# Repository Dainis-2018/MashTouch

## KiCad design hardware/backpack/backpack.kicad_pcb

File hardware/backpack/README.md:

# I/O backpack (KiCad 10)

The MCU-less board that plugs into J8 of the Waveshare ESP32‑S3‑Touch‑LCD‑3.5. What it does and why: `docs/design.md` (*I/O backpack PCB*). Mechanics, zones and connector order: `docs/backpack-layout.md`.

| File | Contents |
|---|---|
| `backpack.kicad_pro` | the project: open this in KiCad |
| `backpack.kicad_sch` | the whole schematic on one A3 sheet, **wired**: J8 in the middle, outputs (OUT1–4, PWR1–2, JP1) on the left, the 12 V input and buck on top, PT100 (2× MAX31865, JP2/JP3, J4), 1‑Wire, level and the front panel (TCA9535, J7) on the right, decoupling, power flags and holes at the bottom. Power nets are symbols; every other net has one label with its name |
| `backpack.kicad_sym`, `sym-lib-table` | project symbols: MOSFETs, the ICs, J8 and the terminals, with the pins where the sheet needs them |
| `backpack.kicad_pcb` | outline with the antenna notch, holes, J8 and terminals at their measured positions; all parts placed (zones and reasons in `docs/backpack-layout.md`), silkscreen labels done, **routed** (two layers, GND pour on both) |
| `backpack.pretty/`, `fp-lib-table` | project footprints: the J8 header for the back side |
| `netlist-reference.txt` | the reviewed netlist, pin by pin, for `tools/kicad/netcheck.js` |
| `parts.csv` | the part chosen for each Value + Footprint (Value `*` = any): `smt` (assembled by the PCB house) / `hand` / `none`, manufacturer, MPN, description, LCSC number, note. **Edit this**, not `bom.csv` |
| `bom.csv` | grouped BOM of all parts, generated by `tools/kicad/fab_export.js` from the schematic and `parts.csv` |
| `fab/` | order files, generated, not in git: `backpack-gerbers.zip`, `backpack-cpl.csv`, `backpack-bom-pcbway.csv`, `backpack-bom-jlc.csv` |
| `../../docs/img/backpack-schematic.svg` | the sheet exported as SVG, for reading without KiCad |

## State (2026‑11‑17)

- **Schematic:** complete first version, wired on one sheet, ERC clean. Converted from the label-per-pin sheet on 2026‑11‑17: same 358 pins on the same nets (only the former global names gained a `/`), same symbol UUIDs and fields, so the PCB stayed linked.
- **PCB:** placed, labelled and **routed** (2026‑11‑17). Placement: buck next to J8 pin 2, TCA9535 next to the I2C pins, test points and J9 below J8. Silkscreen names every terminal position and jumper setting; references are on the Fab layer only. Routing: power, 3 A paths, the buck loop, both RTD front ends and the level input by hand (locked tracks), the rest by Freerouting, then GND pours on both layers. 78 GND vias: one at every SMD ground pad, a few in the buck area and only the stitching vias needed to join the pour islands (the 2.5 mm stitching grid was removed again). Net classes (width / clearance): Power 0.8 / 0.25 mm (+12V, +5V, OUT_V, buck switch node, PWR outputs), Drive 0.5 / 0.25 mm (OUT/PWR loads and gates, LED ring drivers), Logic3V3 0.3 / 0.25 mm, Panel 0.25 / 0.2 mm (buttons, LED rings, I2C around the TCA9535, which need the tighter spacing), default (incl. GND) 0.25 / 0.25 mm; GND pour 0.3 mm from other nets. Current paths: 12 V input 3 mm, 12 V trunk 3 mm (2 mm after the PWR2 branch), PTC → terminal 2 mm, MOSFET tab → terminal 2 mm, three ground vias per MOSFET source; J3 GND, Q6/Q7 sources and J7/J8/JP2/JP3 ground pins connect solidly to the pour. **DRC: 0 violations, 0 unconnected, 0 schematic parity issues.** Not yet reviewed by a person: look it over in KiCad before ordering.
- **Parts (2026‑11‑18):** every assembled part has a manufacturer and MPN in `parts.csv`, and an LCSC number (JLCPCB basic parts where one exists) except R23/R25, the 430 Ω 0.1 % thin-film RREF (Panasonic ERA‑6AEB431V; not stocked at LCSC). Board house: PCBWay. Check stock at order time.
- **Pad/net check (2026‑11‑18):** all 358 PCB pads carry the same net as a fresh netlist exported from the schematic; DRC with schematic parity is clean.
- **Hand-soldered:** terminals (J1–J5), J7, J8, J9, JP1–JP3, the fuse holder F1.

## Things to know

- **Wires connect wherever a pin end touches them.** Dropping a part onto a passing wire joins it to that net without any warning from ERC. After every schematic edit, run `tools/kicad/netcheck.js` (below) and read what it lists.
- **J8** is on the back layer (B.Cu) and uses the project footprint `backpack:PinHeader_2x16_P2.54mm_Vertical_Bottom` from `backpack.pretty/` (listed in the project `fp-lib-table`): the standard 2×16 header mirrored, because flipping the standard one would swap the odd/even rows. Keep the footprint locked. See `docs/backpack-layout.md`, *Orientation*.
- **J7** is a top-entry JST PH (B6B‑PH‑K): the plug goes in from the box side.
- The terminals are numbered so that their labels read left to right (top edge) and top to bottom (side edges) with the plug openings facing out.
- **PWR_FLAGs** (bottom of the sheet) tell ERC that +12V, +5V, +3V3 and GND are supplied (J3, the buck and the panel).
- **Library tables:** on a fresh KiCad install, open KiCad once so it creates its global symbol and footprint library tables. Until then ERC and DRC also list "library not in the configuration" warnings.
- **Generators:** `tools/kicad/backpack_sch.js` and `backpack_pcb.py` made the first versions; `backpack_overview.js` (with `backpack_draw.js`, `backpack_kicad.js`) made the wired sheet. They all overwrite their files: **edit in KiCad** and don't rerun them. The placement and routing scripts are in `tools/kicad/route/` (README there); they also overwrite tracks.

## Ordering (PCBWay)

```
node ../../tools/kicad/fab_export.js     # writes fab/ and bom.csv; exit 1 if a part has no row in parts.csv
```

1. PCB: upload `fab/backpack-gerbers.zip`. 2 layers, 1.6 mm FR‑4, 1 oz copper is enough (the 3 A paths are 2–3 mm wide), HASL lead-free or ENIG.
2. Assembly: turnkey, **top side only, SMD only**. Upload `backpack-bom-pcbway.csv` and `backpack-cpl.csv`. PCBWay sources the parts by MPN and asks before substituting; R23/R25 must stay 430 Ω **0.1 %** thin film.
3. PCBWay's engineers check rotations and polarity and send questions or a placement preview: compare pin 1 of the SOT‑23/SOT‑23‑6, TQFN, TSSOP and DPAK parts, the electrolytic's polarity and every diode/LED cathode with the PCB in KiCad.
4. The hand-soldered parts (terminals with their plugs, J7, J8, J9, JP1–JP3 with shunts, F1 with its fuse) are not in the assembly files: order them separately. The J7 cable is a pre-crimped 6‑pin JST PH.

`backpack-bom-jlc.csv` (LCSC numbers, same CPL) is there too in case the board goes to JLCPCB; R23/R25 then have to be chosen in its BOM tool.

## Checks

After a schematic edit:

```
node ../../tools/kicad/netcheck.js            # lists every pin that changed net; exit 1 if any
node ../../tools/kicad/netcheck.js --update   # once all listed changes are intended
```

Then Update PCB from Schematic (F8) and:

```
kicad-cli sch erc --severity-all backpack.kicad_sch
kicad-cli pcb drc --severity-all --schematic-parity backpack.kicad_pcb
kicad-cli sch export svg -o . backpack.kicad_sch    # then move backpack.svg to ../../docs/img/backpack-schematic.svg
```

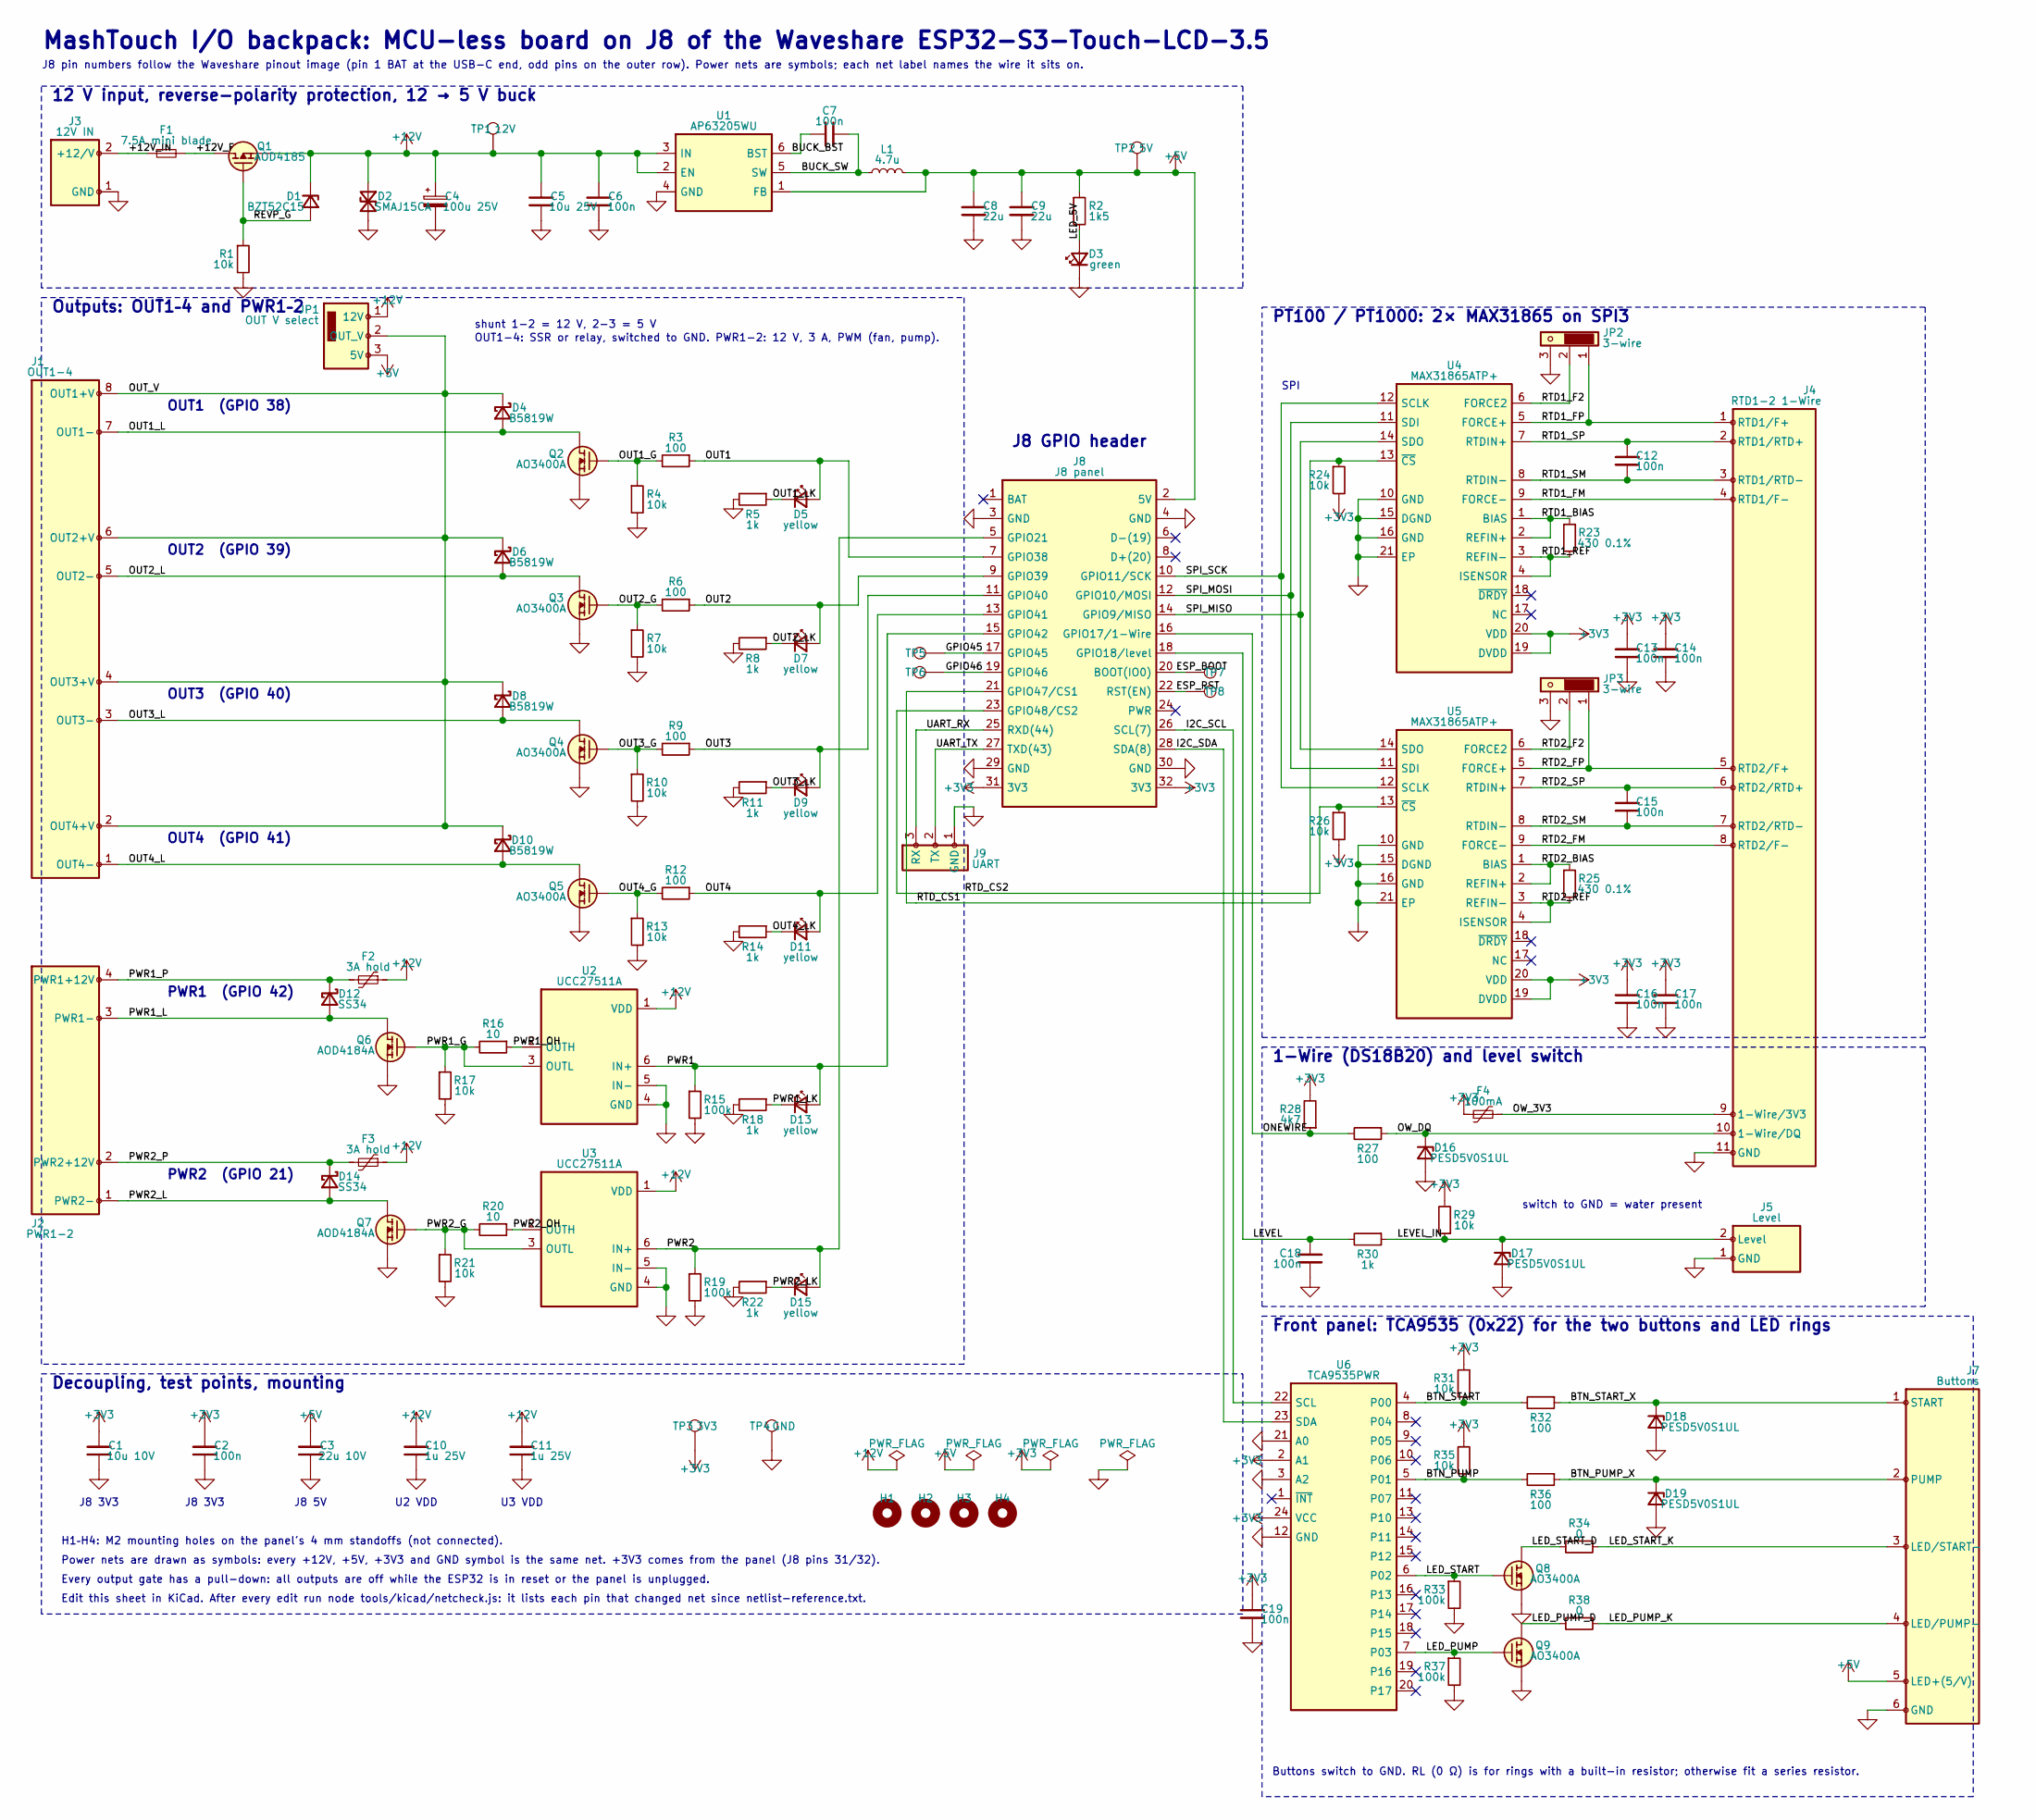
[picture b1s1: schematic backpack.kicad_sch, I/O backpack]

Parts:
C1: 10u 10V; C_0805_2012Metric; MPN X5R 10 uF 10 V 0805
C2, C6, C7, C13, C14, C16, C17, C18, C19: 100n; C_0603_1608Metric
C3: 22u 10V; C_1206_3216Metric; MPN X5R 22 uF 25 V 1206
C4: 100u 25V; CP_Elec_6.3x7.7; MPN Al electrolytic 100 uF 25 V 6.3x7.7
C5: 10u 25V; C_1206_3216Metric; MPN X7R 10 uF 25 V 1206
C8, C9: 22u; C_1206_3216Metric; MPN X5R 22 uF 25 V 1206
C10, C11: 1u 25V; C_0805_2012Metric
C12, C15: 100n; C_0805_2012Metric
D1: BZT52C15; D_SOD-123; MPN BZT52C15 (15 V)
D2: SMAJ15CA; D_SMA; MPN SMAJ15CA
D3: green; LED_0603_1608Metric
D4, D6, D8, D10: B5819W; D_SOD-123; MPN B5819W
D5, D7, D9, D11, D13, D15: yellow; LED_0603_1608Metric
D12, D14: SS34; D_SMA; MPN SS34
D16, D17, D18, D19: PESD5V0S1UL; D_SOD-882; MPN PESD5V0S1UL
F1: 7.5A mini blade; Fuseholder_Blade_Mini_Keystone_3568; MPN Keystone 3568 holder + 7.5 A mini blade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
F2, F3: 3A hold; Fuse_2920_7451Metric; MPN PTC 2920, hold 3 A, >= 16 V
F4: 100mA; Fuse_0805_2012Metric; MPN PTC 0805 hold 0.1 A
H1, H2, H3, H4: M2; MountingHole_2.2mm_M2
J1: OUT1-4; PhoenixContact_MC_1,5_8-G-3.5_1x08_P3.50mm_Horizontal; MPN Phoenix MC 1,5/8-G-3,5 + plug MC 1,5/8-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
J2: PWR1-2; PhoenixContact_MC_1,5_4-G-3.5_1x04_P3.50mm_Horizontal; MPN Phoenix MC 1,5/4-G-3,5 + plug MC 1,5/4-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
J3: 12V IN; PhoenixContact_MC_1,5_2-G-3.5_1x02_P3.50mm_Horizontal; MPN Phoenix MC 1,5/2-G-3,5 + plug MC 1,5/2-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
J4: RTD1-2 1-Wire; PhoenixContact_MC_1,5_11-G-3.5_1x11_P3.50mm_Horizontal; MPN Phoenix MC 1,5/11-G-3,5 + plug MC 1,5/1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
J5: Level; PhoenixContact_MC_1,5_2-G-3.5_1x02_P3.50mm_Horizontal; MPN Phoenix MC 1,5/2-G-3,5 + plug MC 1,5/2-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
J7: Buttons; JST_PH_B6B-PH-K_1x06_P2.00mm_Vertical; MPN JST B6B-PH-K
J8: J8 panel; PinHeader_2x16_P2.54mm_Vertical_Bottom; MPN 2x16 2.54 mm male header, short mating 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
J9: UART; PinHeader_1x03_P2.54mm_Vertical
JP1: OUT V select; PinHeader_1x03_P2.54mm_Vertical
JP2, JP3: 3-wire; PinHeader_1x03_P2.54mm_Vertical
L1: 4.7u; L_Bourns_SRN6045TA; MPN Bourns SRN6045TA-4R7M (or 6x6 mm 4.7 uH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
Q1: AOD4185; TO-252-2; MPN AOD4185 (P-ch -40 V, DPAK)
Q2, Q3, Q4, Q5, Q8, Q9: AO3400A; SOT-23; MPN AO3400A
Q6, Q7: AOD4184A; TO-252-2; MPN AOD4184A (N-ch 40 V, DPAK)
R1, R4, R7, R10, R13, R17, R21, R24, R26, R29, R31, R35: 10k; R_0603_1608Metric
R2: 1k5; R_0603_1608Metric
R3, R6, R9, R12, R27, R32, R36: 100; R_0603_1608Metric
R5, R8, R11, R14, R18, R22, R30: 1k; R_0603_1608Metric
R15, R19, R33, R37: 100k; R_0603_1608Metric
R16, R20: 10; R_0603_1608Metric
R23, R25: 430 0.1%; R_0805_2012Metric; MPN 430 R 0.1 % 25 ppm 0805
R28: 4k7; R_0603_1608Metric
R34, R38: 0; R_0805_2012Metric
TP1: 12V; TestPoint_Pad_D1.5mm
TP2: 5V; TestPoint_Pad_D1.5mm
TP3: 3V3; TestPoint_Pad_D1.5mm
TP4: GND; TestPoint_Pad_D1.5mm
TP5: GPIO45; TestPoint_Pad_D1.5mm
TP6: GPIO46; TestPoint_Pad_D1.5mm
TP7: ESP_BOOT; TestPoint_Pad_D1.5mm
TP8: ESP_RST; TestPoint_Pad_D1.5mm
U1: AP63205WU; TSOT-23-6; MPN AP63205WU-7; LCSC C2071056
U2, U3: UCC27511A; SOT-23-6; MPN UCC27511ADBVR; LCSC C2676982
U4, U5: MAX31865ATP+; TQFN-20-1EP_5x5mm_P0.65mm_EP3.25x3.25mm; MPN MAX31865ATP+; LCSC C404011
U6: TCA9535PWR; TSSOP-24_4.4x7.8mm_P0.65mm; MPN TCA9535PWR; LCSC C130204

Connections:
+3V3: C1.1, C2.1, C13.1, C14.1, C16.1, C17.1, C19.1, F4.1, J8.31 (3V3), J8.32 (3V3), R24.2, R26.2, R28.2, R29.2, R31.2, R35.2, TP3.1 (1_1), U4.19 (DVDD), U4.20 (VDD), U5.19 (DVDD), U5.20 (VDD), U6.2 (A1), U6.24 (VCC)
+5V: C3.1, C8.1, C9.1, J7.5 (LED+(5/V)), J8.2 (5V), JP1.3 (5V), L1.2, R2.1, TP2.1 (1_1), U1.1 (FB)
+12V: C4.1, C5.1, C6.1, C10.1, C11.1, D1.1 (K), D2.1 (A1), F2.1, F3.1, JP1.1 (12V), Q1.3 (S), TP1.1 (1_1), U1.2 (EN), U1.3 (IN), U2.1 (VDD), U3.1 (VDD)
/+12V_F: F1.2, Q1.2 (D)
/+12V_IN: F1.1, J3.2 (+12/V)
/BTN_PUMP: R35.1, R36.2, U6.5 (P01)
/BTN_PUMP_X: D19.1 (K), J7.2 (PUMP), R36.1
/BTN_START: R31.1, R32.2, U6.4 (P00)
/BTN_START_X: D18.1 (K), J7.1 (START), R32.1
/BUCK_BST: C7.1, U1.6 (BST)
/BUCK_SW: C7.2, L1.1, U1.5 (SW)
/ESP_BOOT: J8.20 (BOOT(IO0)), TP7.1 (1_1)
/ESP_RST: J8.22 (RST(EN)), TP8.1 (1_1)
/GPIO45: J8.17 (GPIO45), TP5.1 (1_1)
/GPIO46: J8.19 (GPIO46), TP6.1 (1_1)
/I2C_SCL: J8.26 (SCL(7)), U6.22 (SCL)
/I2C_SDA: J8.28 (SDA(8)), U6.23 (SDA)
/LED_5V: D3.2 (A), R2.2
/LED_PUMP: Q9.1 (G), R37.1, U6.7 (P03)
/LED_PUMP_D: Q9.3 (D), R38.2
/LED_PUMP_K: J7.4 (LED/PUMP−), R38.1
/LED_START: Q8.1 (G), R33.1, U6.6 (P02)
/LED_START_D: Q8.3 (D), R34.2
/LED_START_K: J7.3 (LED/START−), R34.1
/LEVEL: C18.1, J8.18 (GPIO18/level), R30.2
/LEVEL_IN: D17.1 (K), J5.2 (Level), R29.1, R30.1
/ONEWIRE: J8.16 (GPIO17/1-Wire), R27.2, R28.1
/OUT1: D5.2 (A), J8.7 (GPIO38), R3.1
/OUT1_G: Q2.1 (G), R3.2, R4.1
/OUT1_L: D4.2 (A), J1.7 (OUT1−), Q2.3 (D)
/OUT1_LK: D5.1 (K), R5.1
/OUT2: D7.2 (A), J8.9 (GPIO39), R6.1
/OUT2_G: Q3.1 (G), R6.2, R7.1
/OUT2_L: D6.2 (A), J1.5 (OUT2−), Q3.3 (D)
/OUT2_LK: D7.1 (K), R8.1
/OUT3: D9.2 (A), J8.11 (GPIO40), R9.1
/OUT3_G: Q4.1 (G), R9.2, R10.1
/OUT3_L: D8.2 (A), J1.3 (OUT3−), Q4.3 (D)
/OUT3_LK: D9.1 (K), R11.1
/OUT4: D11.2 (A), J8.13 (GPIO41), R12.1
/OUT4_G: Q5.1 (G), R12.2, R13.1
/OUT4_L: D10.2 (A), J1.1 (OUT4−), Q5.3 (D)
/OUT4_LK: D11.1 (K), R14.1
/OUT_V: D4.1 (K), D6.1 (K), D8.1 (K), D10.1 (K), J1.2 (OUT4+V), J1.4 (OUT3+V), J1.6 (OUT2+V), J1.8 (OUT1+V), JP1.2 (OUT_V)
/OW_3V3: F4.2, J4.9 (1-Wire/3V3)
/OW_DQ: D16.1 (K), J4.10 (1-Wire/DQ), R27.1
/PWR1: D13.2 (A), J8.15 (GPIO42), R15.1, U2.6 (IN+)
/PWR1_G: Q6.1 (G), R16.2, R17.1, U2.3 (OUTL)
/PWR1_L: D12.2 (A), J2.3 (PWR1−), Q6.2 (D)
/PWR1_LK: D13.1 (K), R18.1
/PWR1_OH: R16.1, U2.2 (OUTH)
/PWR1_P: D12.1 (K), F2.2, J2.4 (PWR1+12V)
/PWR2: D15.2 (A), J8.5 (GPIO21), R19.1, U3.6 (IN+)
/PWR2_G: Q7.1 (G), R20.2, R21.1, U3.3 (OUTL)
/PWR2_L: D14.2 (A), J2.1 (PWR2−), Q7.2 (D)
/PWR2_LK: D15.1 (K), R22.1
/PWR2_OH: R20.1, U3.2 (OUTH)
/PWR2_P: D14.1 (K), F3.2, J2.2 (PWR2+12V)
/REVP_G: D1.2 (A), Q1.1 (G), R1.1
/RTD1_BIAS: R23.1, U4.1 (BIAS), U4.2 (REFIN+)
/RTD1_F2: JP2.2, U4.6 (FORCE2)
/RTD1_FM: J4.4 (RTD1/F−), U4.9 (FORCE−)
/RTD1_FP: J4.1 (RTD1/F+), JP2.1, U4.5 (FORCE+)
/RTD1_REF: R23.2, U4.3 (REFIN−), U4.4 (ISENSOR)
/RTD1_SM: C12.2, J4.3 (RTD1/RTD−), U4.8 (RTDIN−)
/RTD1_SP: C12.1, J4.2 (RTD1/RTD+), U4.7 (RTDIN+)
/RTD2_BIAS: R25.1, U5.1 (BIAS), U5.2 (REFIN+)
/RTD2_F2: JP3.2, U5.6 (FORCE2)
/RTD2_FM: J4.8 (RTD2/F−), U5.9 (FORCE−)
/RTD2_FP: J4.5 (RTD2/F+), JP3.1, U5.5 (FORCE+)
/RTD2_REF: R25.2, U5.3 (REFIN−), U5.4 (ISENSOR)
/RTD2_SM: C15.2, J4.7 (RTD2/RTD−), U5.8 (RTDIN−)
/RTD2_SP: C15.1, J4.6 (RTD2/RTD+), U5.7 (RTDIN+)
/RTD_CS1: J8.21 (GPIO47/CS1), R24.1, U4.13 (~CS)
/RTD_CS2: J8.23 (GPIO48/CS2), R26.1, U5.13 (~CS)
/SPI_MISO: J8.14 (GPIO9/MISO), U4.14 (SDO), U5.14 (SDO)
/SPI_MOSI: J8.12 (GPIO10/MOSI), U4.11 (SDI), U5.11 (SDI)
/SPI_SCK: J8.10 (GPIO11/SCK), U4.12 (SCLK), U5.12 (SCLK)
/UART_RX: J8.25 (RXD(44)), J9.3 (RX)
/UART_TX: J8.27 (TXD(43)), J9.2 (TX)
GND: C1.2, C2.2, C3.2, C4.2, C5.2, C6.2, C8.2, C9.2, C10.2, C11.2, C13.2, C14.2, C16.2, C17.2, C18.2, C19.2, D2.2 (A2), D3.1 (K), D16.2 (A), D17.2 (A), D18.2 (A), D19.2 (A), J3.1 (GND), J4.11 (GND), J5.1 (GND), J7.6 (GND), J8.3 (GND), J8.4 (GND), J8.29 (GND), J8.30 (GND), J9.1 (GND), JP2.3, JP3.3, Q2.2 (S), Q3.2 (S), Q4.2 (S), Q5.2 (S), Q6.3 (S), Q7.3 (S), Q8.2 (S), Q9.2 (S), R1.2, R4.2, R5.2, R7.2, R8.2, R10.2, R11.2, R13.2, R14.2, R15.2, R17.2, R18.2, R19.2, R21.2, R22.2, R33.2, R37.2, TP4.1 (1_1), U1.4 (GND), U2.4 (GND), U2.5 (IN−), U3.4 (GND), U3.5 (IN−), U4.10 (GND), U4.15 (DGND), U4.16 (GND), U4.21 (EP), U5.10 (GND), U5.15 (DGND), U5.16 (GND), U5.21 (EP), U6.3 (A2), U6.12 (GND), U6.21 (A0)

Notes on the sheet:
MashTouch I/O backpack: MCU-less board on J8 of the Waveshare ESP32-S3-Touch-LCD-3.5
J8 pin numbers follow the Waveshare pinout image (pin 1 BAT at the USB-C end, odd pins on the outer row). Power nets are symbols; each net label names the wire it sits on.
12 V input, reverse-polarity protection, 12 → 5 V buck
J8 GPIO header
Outputs: OUT1–4 and PWR1–2
OUT1 (GPIO 38)
OUT2 (GPIO 39)
OUT3 (GPIO 40)
OUT4 (GPIO 41)
PWR1 (GPIO 42)
PWR2 (GPIO 21)
shunt 1-2 = 12 V, 2-3 = 5 V
OUT1-4: SSR or relay, switched to GND. PWR1-2: 12 V, 3 A, PWM (fan, pump).
PT100 / PT1000: 2× MAX31865 on SPI3
SPI
1-Wire (DS18B20) and level switch
switch to GND = water present
Front panel: TCA9535 (0x22) for the two buttons and LED rings
Buttons switch to GND. RL (0 Ω) is for rings with a built-in resistor; otherwise fit a series resistor.
Decoupling, test points, mounting
J8 3V3
J8 5V
U2 VDD
U3 VDD
H1–H4: M2 mounting holes on the panel's 4 mm standoffs (not connected).
Power nets are drawn as symbols: every +12V, +5V, +3V3 and GND symbol is the same net. +3V3 comes from the panel (J8 pins 31/32).
Every output gate has a pull-down: all outputs are off while the ESP32 is in reset or the panel is unplugged.
Edit this sheet in KiCad. After every edit run node tools/kicad/netcheck.js: it lists each pin that changed net since netlist-reference.txt.

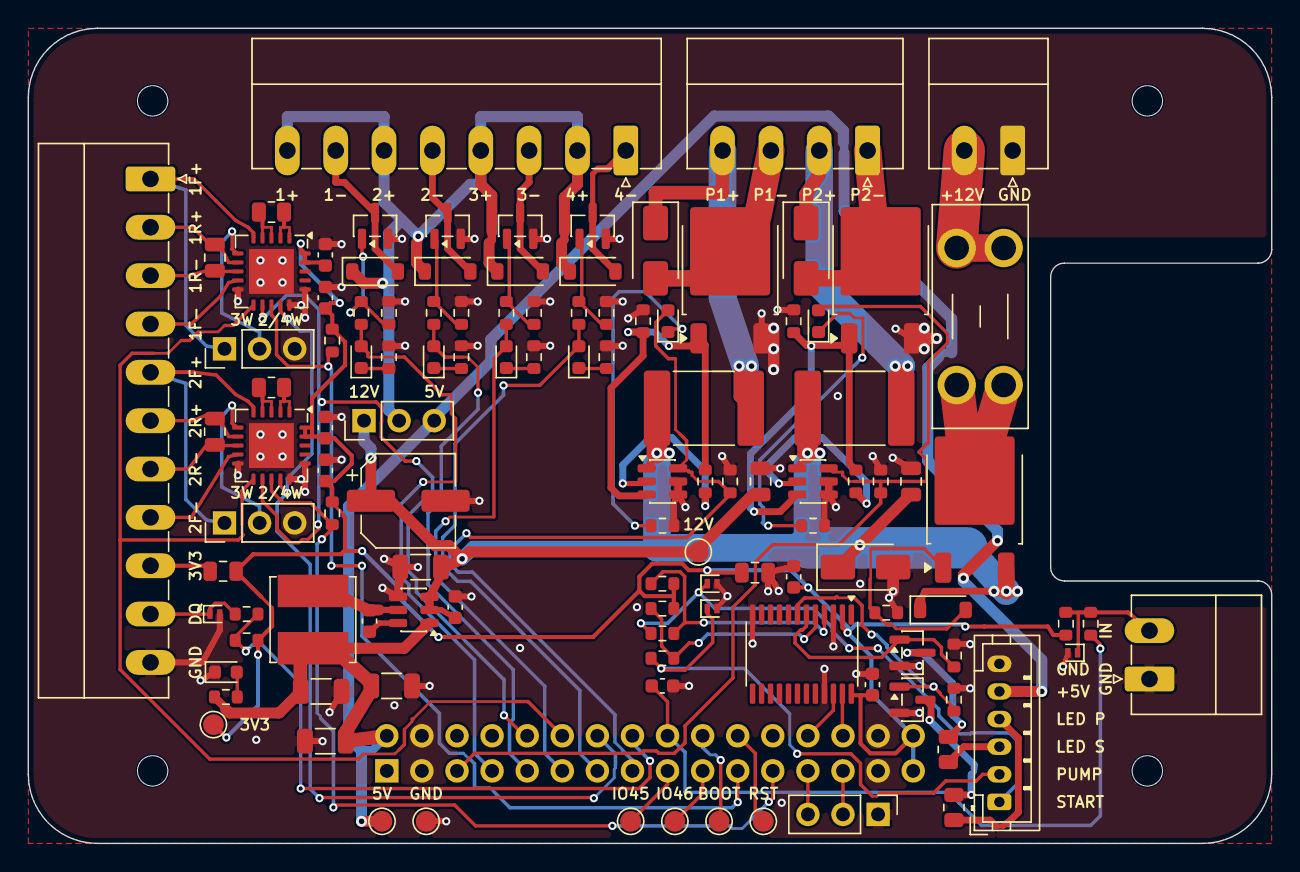
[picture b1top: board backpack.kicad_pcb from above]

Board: 2 copper layers, 90.0 x 59.0 mm, 119 parts (1 on the bottom side), 81 nets.

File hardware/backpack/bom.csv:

"Refs","Value","Footprint","Manufacturer","MPN","Description","LCSC","Fit","Note","Qty"
"C1","10u 10V","Capacitor_SMD:C_0805_2012Metric","Samsung","CL21A106KAYNNNE","MLCC 10 uF 25 V X5R 0805","C15850","smt","","1"
"C2,C6,C7,C13,C14,C16,C17,C18,C19","100n","Capacitor_SMD:C_0603_1608Metric","YAGEO","CC0603KRX7R9BB104","MLCC 100 nF 50 V X7R 0603","C14663","smt","","9"
"C3","22u 10V","Capacitor_SMD:C_1206_3216Metric","Samsung","CL31A226KAHNNNE","MLCC 22 uF 25 V X5R 1206","C12891","smt","","1"
"C4","100u 25V","Capacitor_SMD:CP_Elec_6.3x7.7","Panasonic","EEE-FK1E101XP","Al electrolytic 100 uF 25 V 6.3x7.7 mm, 105 C","C128510","smt","polarised","1"
"C5","10u 25V","Capacitor_SMD:C_1206_3216Metric","Samsung","CL31A106KBHNNNE","MLCC 10 uF 50 V X5R 1206","C13585","smt","","1"
"C8,C9","22u","Capacitor_SMD:C_1206_3216Metric","Samsung","CL31A226KAHNNNE","MLCC 22 uF 25 V X5R 1206","C12891","smt","","2"
"C10,C11","1u 25V","Capacitor_SMD:C_0805_2012Metric","Samsung","CL21B105KBFNNNE","MLCC 1 uF 50 V X7R 0805","C28323","smt","","2"
"C12,C15","100n","Capacitor_SMD:C_0805_2012Metric","YAGEO","CC0805KRX7R9BB104","MLCC 100 nF 50 V X7R 0805","C49678","smt","RTD filter Cf; 10 nF for PT1000","2"
"D1","BZT52C15","Diode_SMD:D_SOD-123","MDD","BZT52C15","Zener 15 V 500 mW SOD-123","C173427","smt","gate clamp","1"
"D2","SMAJ15CA","Diode_SMD:D_SMA","Littelfuse","SMAJ15CA","TVS bidirectional 15 V 400 W SMA","C223985","smt","","1"
"D3","green","LED_SMD:LED_0603_1608Metric","Everlight","19-217/GHC-YR1S2/3T","LED green 0603","C72043","smt","5 V on; any 0603 green LED","1"
"D4,D6,D8,D10","B5819W","Diode_SMD:D_SOD-123","CJ","B5819W SL","Schottky 40 V 1 A SOD-123","C8598","smt","flyback","4"
"D5,D7,D9,D11,D13,D15","yellow","LED_SMD:LED_0603_1608Metric","Everlight","19-213/Y2C-CQ2R2L/3T","LED yellow 0603","C72038","smt","output indicators; any 0603 yellow LED","6"
"D12,D14","SS34","Diode_SMD:D_SMA","MDD","SS34","Schottky 40 V 3 A SMA","C8678","smt","flyback","2"
"D16,D17,D18,D19","PESD5V0S1UL","Diode_SMD:D_SOD-882","Nexperia","PESD5V0S1UL,315","ESD diode 5 V SOD-882","C85402","smt","","4"
"F1","7.5A mini blade","Fuse:Fuseholder_Blade_Mini_Keystone_3568","Keystone","3568","mini blade fuse holder, PCB + 7.5 A mini blade fuse","","hand","","1"
"F2,F3","3A hold","Fuse:Fuse_2920_7451Metric","TLC Electronic","TLC-LSMD300D","PTC fuse 3 A hold, 24 V, 2920","C262042","smt","any 2920 PTC 3 A hold >= 16 V (e.g. Littelfuse 2920L300/24)","2"
"F4","100mA","Fuse:Fuse_0805_2012Metric","TECHFUSE","SMD0805-010-24V","PTC fuse 0.1 A hold, 24 V, 0805","C70055","smt","1-Wire sensor supply; e.g. Littelfuse 0805L010/24","1"
"H1,H2,H3,H4","M2","MountingHole:MountingHole_2.2mm_M2","","","","","none","","4"
"J1","OUT1-4","Connector_Phoenix_MC:PhoenixContact_MC_1,5_8-G-3.5_1x08_P3.50mm_Horizontal","Phoenix Contact","MC 1,5/8-G-3,5","pluggable header 8-pin 3.5 mm + plug MC 1,5/8-ST-3,5","","hand","or a 3.5 mm 15EDG equivalent","1"
"J2","PWR1-2","Connector_Phoenix_MC:PhoenixContact_MC_1,5_4-G-3.5_1x04_P3.50mm_Horizontal","Phoenix Contact","MC 1,5/4-G-3,5","pluggable header 4-pin 3.5 mm + plug MC 1,5/4-ST-3,5","","hand","or a 3.5 mm 15EDG equivalent","1"
"J3","12V IN","Connector_Phoenix_MC:PhoenixContact_MC_1,5_2-G-3.5_1x02_P3.50mm_Horizontal","Phoenix Contact","MC 1,5/2-G-3,5","pluggable header 2-pin 3.5 mm + plug MC 1,5/2-ST-3,5","","hand","or a 3.5 mm 15EDG equivalent","1"
"J4","RTD1-2 1-Wire","Connector_Phoenix_MC:PhoenixContact_MC_1,5_11-G-3.5_1x11_P3.50mm_Horizontal","Phoenix Contact","MC 1,5/11-G-3,5","pluggable header 11-pin 3.5 mm + plug MC 1,5/11-ST-3,5","","hand","or a 3.5 mm 15EDG equivalent","1"
"J5","Level","Connector_Phoenix_MC:PhoenixContact_MC_1,5_2-G-3.5_1x02_P3.50mm_Horizontal","Phoenix Contact","MC 1,5/2-G-3,5","pluggable header 2-pin 3.5 mm + plug MC 1,5/2-ST-3,5","","hand","or a 3.5 mm 15EDG equivalent","1"
"J7","Buttons","Connector_JST:JST_PH_B6B-PH-K_1x06_P2.00mm_Vertical","JST","B6B-PH-K-S","PH header 6-pin 2.0 mm vertical; cable: pre-crimped 6-pin JST PH, ordered separately","C131342","hand","1 START, 2 PUMP, 3 LED S-, 4 LED P-, 5 LED+ (5 V), 6 GND","1"
"J8","J8 panel","backpack:PinHeader_2x16_P2.54mm_Vertical_Bottom","","","2x16 2.54 mm male header, short mating pins (<= 4.5 mm), 2.5 mm body","","hand","fitted on the bottom (panel) side; mates with the panel's J8 socket","1"
"J9","UART","Connector_PinHeader_2.54mm:PinHeader_1x03_P2.54mm_Vertical","","","1x03 2.54 mm pin header","","hand","optional, for a USB-UART adapter with Dupont wires; pin 2 = ESP TX (GPIO43), pin 3 = ESP RX (GPIO44)","1"
"JP1","OUT V select","Connector_PinHeader_2.54mm:PinHeader_1x03_P2.54mm_Vertical","","","1x03 2.54 mm pin header + jumper shunt","","hand","","1"
"JP2,JP3","3-wire","Connector_PinHeader_2.54mm:PinHeader_1x03_P2.54mm_Vertical","","","1x03 2.54 mm pin header + jumper shunt","","hand","1-2 = 3-wire, 2-3 = 2/4-wire","2"
"L1","4.7u","Inductor_SMD:L_Bourns_SRN6045TA","Bourns","SRN6045TA-4R7M","power inductor 4.7 uH 6x6 mm, Isat >= 3 A","C2044594","smt","","1"
"Q1","AOD4185","Package_TO_SOT_SMD:TO-252-2","Alpha & Omega","AOD4185","MOSFET P-ch -40 V DPAK","C400894","smt","reverse-polarity protection","1"
"Q2,Q3,Q4,Q5,Q8,Q9","AO3400A","Package_TO_SOT_SMD:SOT-23","Alpha & Omega","AO3400A","MOSFET N-ch 30 V 5.7 A SOT-23","C20917","smt","","6"
"Q6,Q7","AOD4184A","Package_TO_SOT_SMD:TO-252-2","Alpha & Omega","AOD4184A","MOSFET N-ch 40 V DPAK","C99124","smt","","2"
"R1,R4,R7,R10,R13,R17,R21,R24,R26,R29,R31,R35","10k","Resistor_SMD:R_0603_1608Metric","UNI-ROYAL","0603WAF1002T5E","10 k 1 % 0603","C25804","smt","","12"
"R2","1k5","Resistor_SMD:R_0603_1608Metric","UNI-ROYAL","0603WAF1501T5E","1.5 k 1 % 0603","C22843","smt","","1"
"R3,R6,R9,R12,R27,R32,R36","100","Resistor_SMD:R_0603_1608Metric","UNI-ROYAL","0603WAF1000T5E","100 R 1 % 0603","C22775","smt","","7"
"R5,R8,R11,R14,R18,R22,R30","1k","Resistor_SMD:R_0603_1608Metric","UNI-ROYAL","0603WAF1001T5E","1 k 1 % 0603","C21190","smt","","7"
"R15,R19,R33,R37","100k","Resistor_SMD:R_0603_1608Metric","UNI-ROYAL","0603WAF1003T5E","100 k 1 % 0603","C25803","smt","","4"
"R16,R20","10","Resistor_SMD:R_0603_1608Metric","UNI-ROYAL","0603WAF100JT5E","10 R 1 % 0603","C22859","smt","","2"
"R23,R25","430 0.1%","Resistor_SMD:R_0805_2012Metric","Panasonic","ERA-6AEB431V","thin film 430 R 0.1 % 25 ppm 0805","","smt","RREF, must be 0.1 %; 4k3 for PT1000. Alternatives: YAGEO RT0805BRD07430RL / RT0805BRC07430RL","2"
"R28","4k7","Resistor_SMD:R_0603_1608Metric","UNI-ROYAL","0603WAF4701T5E","4.7 k 1 % 0603","C23162","smt","","1"
"R34,R38","0","Resistor_SMD:R_0805_2012Metric","UNI-ROYAL","0805W8F0000T5E","0 R jumper 0805","C17477","smt","series resistor for LED rings without one","2"
"TP1","12V","TestPoint:TestPoint_Pad_D1.5mm","","","","","none","bare pad","1"
"TP2","5V","TestPoint:TestPoint_Pad_D1.5mm","","","","","none","bare pad","1"
"TP3","3V3","TestPoint:TestPoint_Pad_D1.5mm","","","","","none","bare pad","1"
"TP4","GND","TestPoint:TestPoint_Pad_D1.5mm","","","","","none","bare pad","1"
"TP5","GPIO45","TestPoint:TestPoint_Pad_D1.5mm","","","","","none","bare pad","1"
"TP6","GPIO46","TestPoint:TestPoint_Pad_D1.5mm","","","","","none","bare pad","1"
"TP7","ESP_BOOT","TestPoint:TestPoint_Pad_D1.5mm","","","","","none","bare pad","1"
"TP8","ESP_RST","TestPoint:TestPoint_Pad_D1.5mm","","","","","none","bare pad","1"
"U1","AP63205WU","Package_TO_SOT_SMD:TSOT-23-6","Diodes Inc.","AP63205WU-7","buck 5 V 2 A TSOT-23-6","C2071056","smt","","1"
"U2,U3","UCC27511A","Package_TO_SOT_SMD:SOT-23-6","Texas Instruments","UCC27511ADBVR","gate driver SOT-23-6","C2676982","smt","","2"
"U4,U5","MAX31865ATP+","Package_DFN_QFN:TQFN-20-1EP_5x5mm_P0.65mm_EP3.25x3.25mm","Analog Devices","MAX31865ATP+","RTD-to-digital TQFN-20","C404011","smt","","2"
"U6","TCA9535PWR","Package_SO:TSSOP-24_4.4x7.8mm_P0.65mm","Texas Instruments","TCA9535PWR","I2C I/O expander TSSOP-24","C130204","smt","","1"

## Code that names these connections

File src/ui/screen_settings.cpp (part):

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                num("Timeout", "autotune.timeoutMin", 10, 600, 10, 0, "min"),
                flag("Pump on", "autotune.pumpOn")}});
  Section out{"Outputs", {}};
  static const char* names[settings::kOutputChannels] = {"OUT1", "OUT2", "OUT3", "OUT4", "PWR1", "PWR2"};
  static char paths[settings::kOutputChannels][3][24];
  static char labels[settings::kOutputChannels][3][24];
  for (int ch = 0; ch < settings::kOutputChannels; ch++) {
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
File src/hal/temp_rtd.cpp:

// MashTouch - ESP32-S3 touchscreen brew controller
// Copyright (C) 2026 MashTouch contributors
// SPDX-License-Identifier: GPL-3.0-or-later
//
// MAX31865 driver written from the Maxim/Analog Devices datasheet.

#include "temp_rtd.h"

#include <Arduino.h>
#include <SPI.h>
#include <math.h>

#include "board/pins.h"

namespace rtd_temp {
namespace {

// Registers (read address; writes set bit 7)
constexpr uint8_t kRegConfig = 0x00;
constexpr uint8_t kRegRtdMsb = 0x01;       // + LSB at 0x02, bit 0 = fault
constexpr uint8_t kRegHighFaultMsb = 0x03;  // high MSB/LSB, low MSB/LSB
constexpr uint8_t kRegFault = 0x07;
constexpr uint8_t kWrite = 0x80;

// Configuration bits
constexpr uint8_t kCfgBias = 0x80;
constexpr uint8_t kCfgAuto = 0x40;
constexpr uint8_t kCfgOneShot = 0x20;     // self-clearing
constexpr uint8_t kCfg3Wire = 0x10;
constexpr uint8_t kCfgFaultCycle = 0x0C;  // fault detection cycle (unused)
constexpr uint8_t kCfgFaultClear = 0x02;  // self-clearing
constexpr uint8_t kCfg50Hz = 0x01;
constexpr uint8_t kCfgStable = (uint8_t)~(kCfgOneShot | kCfgFaultCycle | kCfgFaultClear);

constexpr uint32_t kReadMs = 250;    // automatic conversions run every ~20 ms
constexpr uint32_t kRetryMs = 5000;  // a missing chip is looked for this often
constexpr uint16_t kRawOpen = 32700; // at full scale: probe or wire open
constexpr uint8_t kFaultsBeforeLoss = 3;  // keep the last value over brief glitches

const int kCsPins[kChannels] = {PIN_MAX31865_CS1, PIN_MAX31865_CS2};

// SPI3: the display has SPI2 to itself.
SPIClass spi(HSPI);
const SPISettings kSpi(1000000, MSBFIRST, SPI_MODE1);
bool spiStarted = false;

struct Channel {
  Config cfg;
  bool configured = false;  // cfg was applied to the chip at least once
  bool present = false;
  uint8_t cfgByte = 0;
  float tempC = kNoReading;
  float ohms = 0;
  uint16_t raw = 0;
  uint8_t fault = 0;
  uint16_t errors = 0;
  uint32_t lastTry = 0;
};
Channel chans[kChannels];
uint32_t lastRead = 0;

bool valid(int ch) { return ch >= 0 && ch < kChannels; }

void startSpi() {
  if (spiStarted) return;
  for (int pin : kCsPins) {
    digitalWrite(pin, HIGH);
    pinMode(pin, OUTPUT);
  }
  spi.begin(PIN_SPI_SCK, PIN_SPI_MISO, PIN_SPI_MOSI, -1);
  spiStarted = true;
}

void transfer(int ch, uint8_t addr, uint8_t* data, int n, bool write) {
  spi.beginTransaction(kSpi);
  digitalWrite(kCsPins[ch], LOW);
  spi.transfer(write ? (uint8_t)(addr | kWrite) : addr);
  for (int i = 0; i < n; i++) {
    uint8_t in = spi.transfer(write ? data[i] : 0xFF);
    if (!write) data[i] = in;
  }
  digitalWrite(kCsPins[ch], HIGH);
  spi.endTransaction();
}

void writeReg(int ch, uint8_t addr, uint8_t v) { transfer(ch, addr, &v, 1, true); }

uint8_t readReg(int ch, uint8_t addr) {
  uint8_t v = 0;
  transfer(ch, addr, &v, 1, false);
  return v;
}

uint8_t configByte(const Config& c) {
  uint8_t b = kCfgBias | kCfgAuto;
  if (c.wires == 3) b |= kCfg3Wire;
  if (c.filter50Hz) b |= kCfg50Hz;
  return b;
}

// Program the chip and check that it answers with what was written.
void apply(int ch) {
  Channel& c = chans[ch];
  c.lastTry = millis();
  c.configured = true;
  startSpi();
  c.cfgByte = configByte(c.cfg);
  // The filter may only change while automatic conversion is off.
  writeReg(ch, kRegConfig, c.cfgByte & ~kCfgAuto);
  // Thresholds wide open: open and short are judged from the reading itself.
  uint8_t thresholds[4] = {0xFF, 0xFF, 0x00, 0x00};
  transfer(ch, kRegHighFaultMsb, thresholds, 4, true);
  writeReg(ch, kRegConfig, c.cfgByte | kCfgFaultClear);
  c.present = (readReg(ch, kRegConfig) & kCfgStable) == c.cfgByte;
  if (!c.present) {
    c.fault = 0;
    c.tempC = kNoReading;
  }
}

void failRead(Channel& c) {
  if (c.errors < UINT16_MAX) c.errors++;
  if (c.errors >= kFaultsBeforeLoss) c.tempC = kNoReading;
}

void readChannel(int ch) {
  Channel& c = chans[ch];
  // A chip that stops answering (unplugged breakout, broken wire on the
  // backpack) no longer returns its configuration.
  if ((readReg(ch, kRegConfig) & kCfgStable) != c.cfgByte) {
    c.present = false;
    c.fault = 0;
    failRead(c);
    return;
  }
  uint8_t b[2] = {0, 0};
  transfer(ch, kRegRtdMsb, b, 2, false);
  uint16_t word = (uint16_t)(b[0] << 8 | b[1]);
  c.raw = word >> 1;
  c.ohms = c.raw * c.cfg.refOhm / 32768.0f;
  uint8_t fault = 0;
  if (word & 1) {
    fault = readReg(ch, kRegFault) & 0xFC;
    writeReg(ch, kRegConfig, c.cfgByte | kCfgFaultClear);
  }
  if (c.raw >= kRawOpen) fault |= kFaultOpen;
  else if (c.ohms < c.cfg.r0 * 0.5f) fault |= kFaultShort;  // below about -120 C
  c.fault = fault;
  if (fault) {
    failRead(c);
    return;
  }
  c.tempC = ohmsToCelsius(c.ohms, c.cfg.r0);
  c.errors = 0;
}

}  // namespace

void configure(int ch, const Config& cfg) {
  if (!valid(ch)) return;
  Channel& c = chans[ch];
  bool same = c.configured && c.cfg.enabled == cfg.enabled && c.cfg.r0 == cfg.r0 && c.cfg.refOhm == cfg.refOhm &&
              c.cfg.wires == cfg.wires && c.cfg.filter50Hz == cfg.filter50Hz;
  if (same) return;
  c.cfg = cfg;
  c.errors = 0;
  c.fault = 0;
  c.tempC = kNoReading;
  if (!cfg.enabled) {
    c.configured = true;
    c.present = false;
    if (spiStarted) writeReg(ch, kRegConfig, 0);  // bias off
    return;
  }
  apply(ch);
}

void recheck() {
  for (int ch = 0; ch < kChannels; ch++)
    if (chans[ch].cfg.enabled) apply(ch);
}

void loop() {
  uint32_t now = millis();
  for (int ch = 0; ch < kChannels; ch++) {
    Channel& c = chans[ch];
    if (c.cfg.enabled && !c.present && now - c.lastTry >= kRetryMs) apply(ch);
  }
  if (now - lastRead < kReadMs) return;
  lastRead = now;
  for (int ch = 0; ch < kChannels; ch++)
    if (chans[ch].cfg.enabled && chans[ch].present) readChannel(ch);
}

bool enabled(int ch) { return valid(ch) && chans[ch].cfg.enabled; }
bool present(int ch) { return valid(ch) && chans[ch].present; }
float temperature(int ch) { return valid(ch) ? chans[ch].tempC : kNoReading; }
float resistance(int ch) { return valid(ch) ? chans[ch].ohms : 0; }
uint16_t raw(int ch) { return valid(ch) ? chans[ch].raw : 0; }
uint8_t faultBits(int ch) { return valid(ch) ? chans[ch].fault : 0; }
uint16_t errorCount(int ch) { return valid(ch) ? chans[ch].errors : 0; }

const char* faultText(uint8_t bits) {
  if (bits & kFaultOpen) return "open circuit";
  if (bits & kFaultShort) return "short circuit";
  if (bits & kFaultRefInHigh) return "REFIN- high (wiring)";
  if (bits & kFaultRefInLow) return "REFIN- low (FORCE- open)";
  if (bits & kFaultRtdInLow) return "RTDIN- low (FORCE- open)";
  if (bits & kFaultVoltage) return "over/undervoltage";
  if (bits & (kFaultHighThreshold | kFaultLowThreshold)) return "out of range";
  return "";
}

float ohmsToCelsius(float ohms, float r0) {
  // IEC 60751 coefficients
  const double A = 3.9083e-3, B = -5.775e-7, C = -4.183e-12;
  double ratio = ohms / r0;
  // R/R0 = 1 + A t + B t^2 for t >= 0: solve the quadratic.
  double disc = A * A - 4 * B * (1 - ratio);
  if (disc < 0) disc = 0;
  double t = (-A + sqrt(disc)) / (2 * B);
  if (ratio >= 1) return (float)t;
  // Below 0 C a C (t - 100) t^3 term is added: refine with Newton's method,
  // starting from the quadratic result (already within a few hundredths).
  for (int i = 0; i < 4; i++) {
    double f = 1 + A * t + B * t * t + C * (t - 100) * t * t * t - ratio;
    double df = A + 2 * B * t + C * (4 * t * t * t - 300 * t * t);
    t -= f / df;
  }
  return (float)t;
}

}  // namespace rtd_temp

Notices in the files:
hardware/backpack/backpack.kicad_sch:
MashTouch (GPL-3.0-or-later)
